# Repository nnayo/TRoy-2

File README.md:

TRoy-2
======

TRoll TRoy 2 fusex

These are the files of the TRoll fusex (fusée expérimentale: experimental rocket) of TRoll association (http://clubtroll.no-ip.org)

This is the second experimental rocket of the association.

Most of the electronics is shared with égère project (http://github.com/nnayo/egere.git).

The mechanic drawings use freecad as many pieces will be 3D-printed.

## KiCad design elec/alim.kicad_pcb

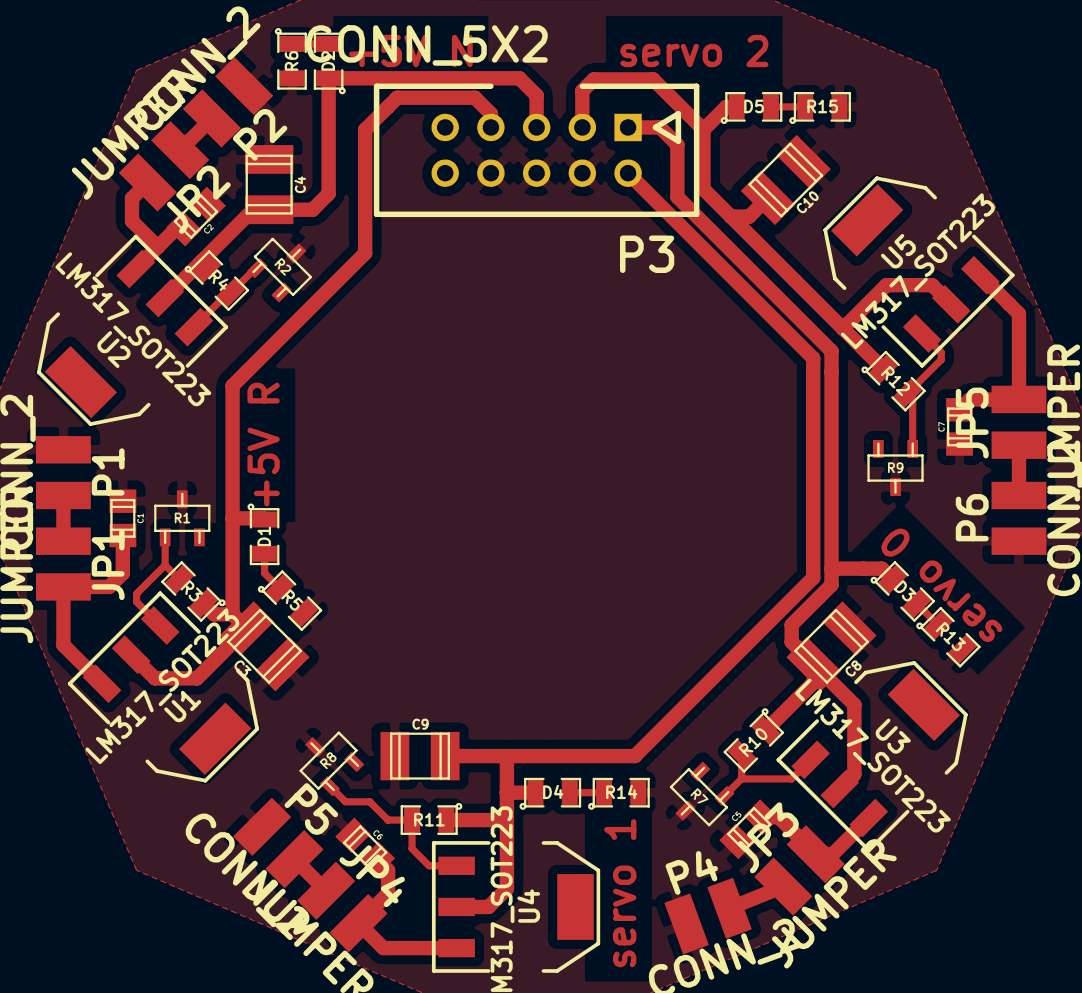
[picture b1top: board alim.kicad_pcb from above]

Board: 2 copper layers, 46 parts (0 on the bottom side), 26 nets.

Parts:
C1, C2, C5, C6, C7: 100nF; c_0805
C3, C4, C8, C9, C10: 100uF; c_1210
D1, D2, D3, D4, D5: LED; SM0805
JP1, JP2, JP3, JP4, JP5: JUMPER; con_2
P1, P2, P4, P5, P6: CONN_2; con_2
P3: CONN_5X2; HE10-10S
R1, R2, R7, R8, R9: 5k; sot23
R3, R4, R5, R6, R10, R11, R12, R13, R14, R15: 240; SM0805
U1, U2, U3, U4, U5: LM317_SOT223; SOT223

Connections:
/+5V N: C4.1, D2.1, P3.5, R4.1, U2.2
/+5V R: C3.1, D1.1, P3.7, R3.1, U1.2
/+6V servo #0: C8.1, D3.1, P3.1, R10.1, U3.2
/+6V servo #1: C9.1, D4.1, P3.2, R11.1, U4.2
/+6V servo #2: C10.1, D5.1, P3.3, R12.1, U5.2
GND: C1.2, C2.2, C3.2, C4.2, C5.2, C6.2, C7.2, C8.2, C9.2, C10.2, P1.1, P2.1, P3.4, P3.6, P3.8, P4.1, P5.1, P6.1, R1.2, R2.2, R5.2, R6.2, R7.2, R8.2, R9.2, R13.2, R14.2, R15.2
unnamed: D2.2, R6.1
unnamed: C2.1, JP2.2, U2.3
unnamed: R2.1, R4.2, U2.1
unnamed: JP2.1, P2.2
unnamed: JP5.1, P6.2
unnamed: D5.2, R15.1
unnamed: R9.1, R12.2, U5.1
unnamed: C7.1, JP5.2, U5.3
unnamed: C6.1, JP4.2, U4.3
unnamed: D1.2, R5.1
unnamed: JP1.1, P1.2
unnamed: JP4.1, P5.2
unnamed: D4.2, R14.1
unnamed: R1.1, R3.2, U1.1
unnamed: C1.1, JP1.2, U1.3
unnamed: JP3.1, P4.2
unnamed: D3.2, R13.1
unnamed: C5.1, JP3.2, U3.3
unnamed: R8.1, R11.2, U4.1
unnamed: R7.1, R10.2, U3.1

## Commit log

2014-01-27 partial refactoring
2014-01-27 mise à jour et envoi de l'avancement
2014-01-27 still refactoring
2014-01-28 elec refactoring done
2014-01-28 cone is work in progress
2014-01-29 cone: WIP
2014-01-29 get ride off rocket_data
2014-01-29 cone still WIP
2014-01-30 cone: first step done\!
2014-02-03 clean-up
2014-02-03 threads first instance
2014-02-04 cone threads done
2014-02-04 locking system done
2014-02-04 servos placed
2014-02-05 final cut of propulsor cut does not work
2014-02-06 basic parachute doors done
2014-02-07 ecope system is mostly done
2014-02-07 propulsor holder is almost done
2014-02-07 propulsor bague done
2014-02-09 add parachute sizing
2014-02-09 elec projet updated by kicad
2014-02-09 add soft taken from egere, it shall be modified
2014-02-09 start wait delay changed to 2s, add more TWI regs surveillance
2014-02-09 add simulator
2014-02-10 I2C bus is connected between every cores
2014-02-10 scons DB is no longer in conf
2014-02-10 frame.py link is relative to prevent changing it every checkout
2014-02-10 makefile is no longer used, it was replaced by scons
2014-02-10 first version
2014-02-11 change simulator name
2014-03-11 simulation is more complete but still not perfect
2014-03-16 TWI bus is working
2014-03-16 suppress some conditions to ease debug
2014-03-16 change color
2014-03-19 turn sc18is600 green led on at start
2014-03-19 better traces
2014-03-19 enable MPU through SC18
2014-03-20 comment correction
2014-03-27 TWI frames are correctly logged
2014-03-27 use I2C address as provided
2014-03-28 update sd for not waiting at start-up and self identifying as a storage node
2014-03-28 enable 1 sd node
2014-03-28 work in progress for clearer frame log
2014-03-30 again trace update
2014-04-11 update docs
